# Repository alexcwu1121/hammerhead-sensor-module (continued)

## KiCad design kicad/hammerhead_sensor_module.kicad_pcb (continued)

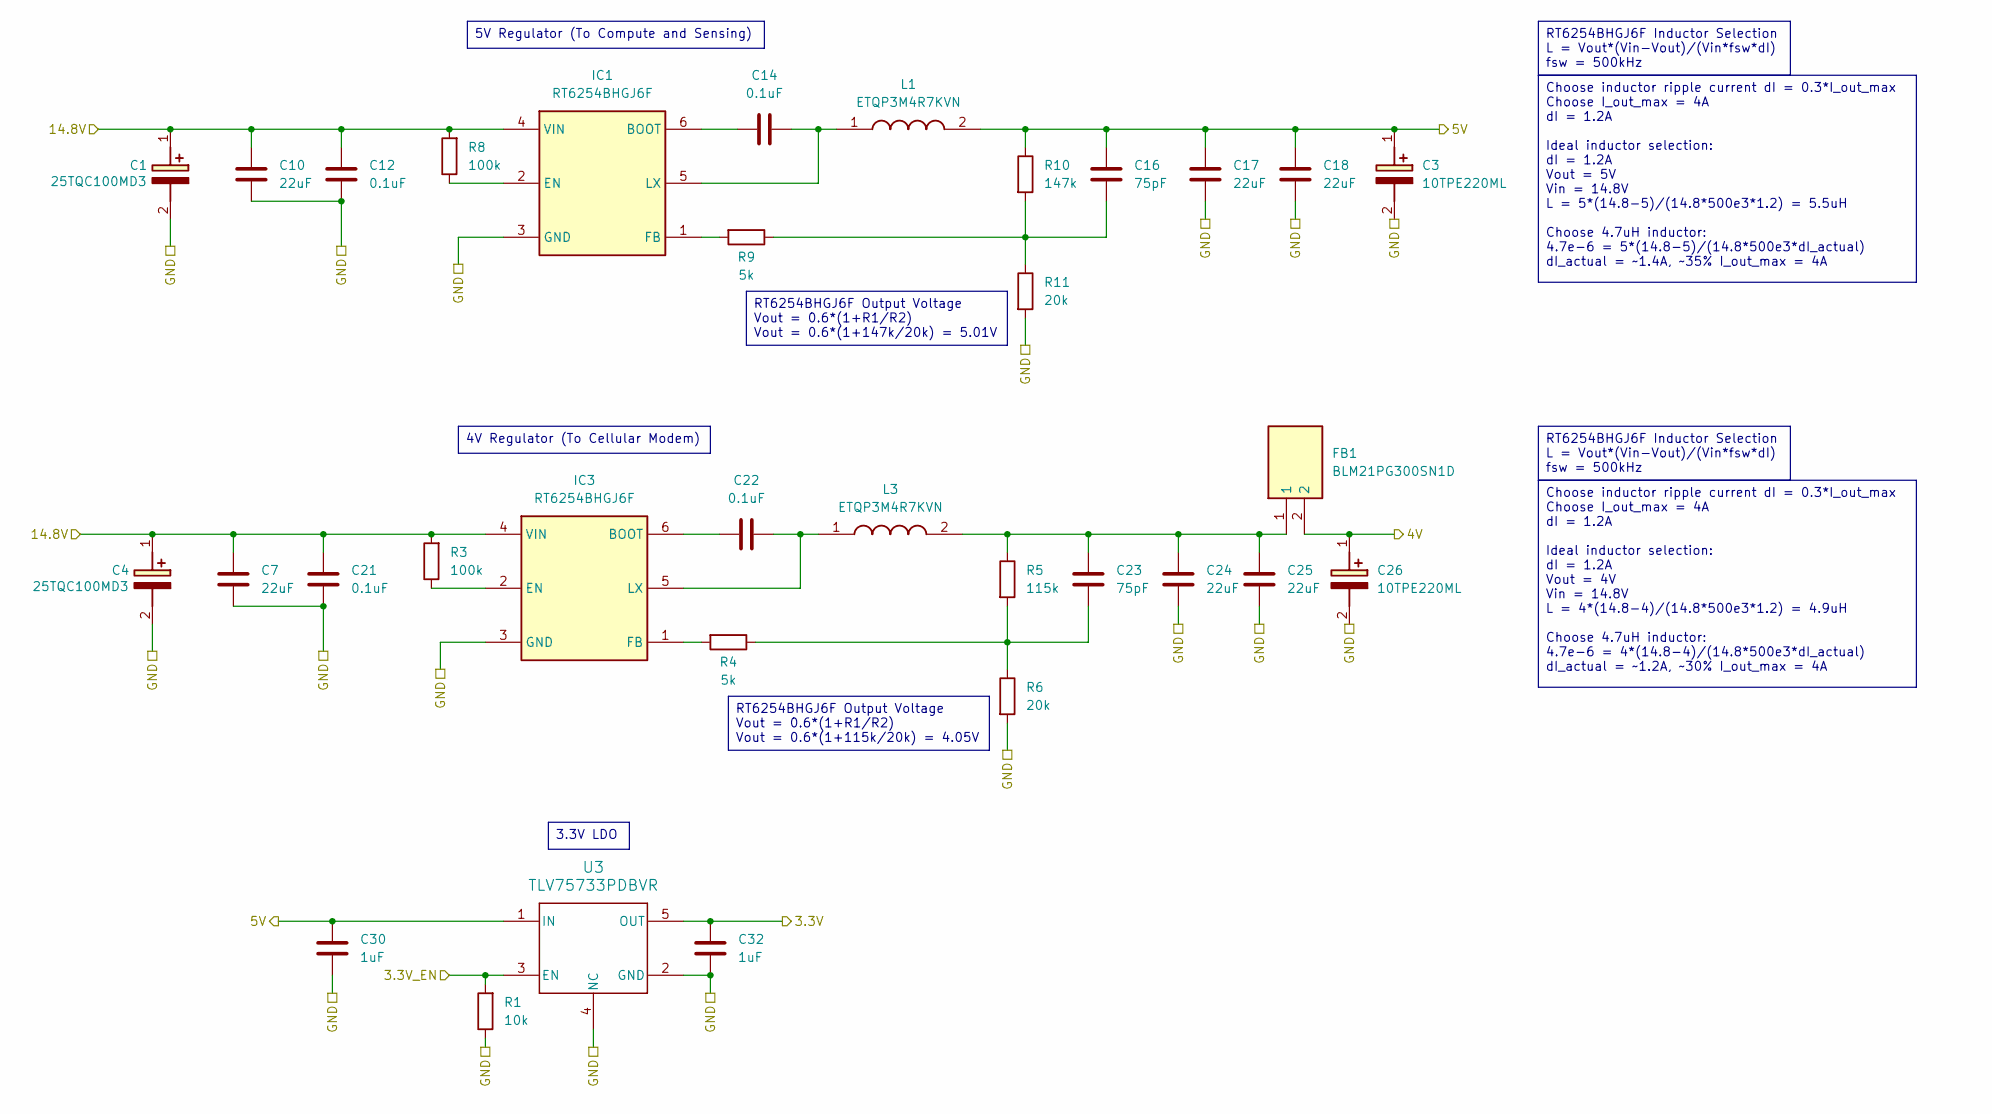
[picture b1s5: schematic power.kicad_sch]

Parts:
C1, C4: 25TQC100MD3; 16TDC150MYF; Manufacturer_Part_Number 25TQC100MD3; Mouser Part Number 667-25TQC100MD3
C3, C26: 10TPE220ML; 16TDC150MYF; Manufacturer_Part_Number 10TPE220ML; Mouser Part Number 667-10TPE220ML
C7, C10, C17, C18, C24, C25: 22uF; C_1206_3216Metric
C12, C14, C21, C22: 0.1uF; C_0201_0603Metric
C16, C23: 75pF; C_0201_0603Metric
C30, C32: 1uF; C_0201_0603Metric
FB1: BLM21PG300SN1D; BEADC2012X105N; Manufacturer_Part_Number BLM21PG300SN1D; Mouser Part Number 81-BLM21P300S
IC1, IC3: RT6254BHGJ6F; SOT95P280X100-6N; Manufacturer_Part_Number RT6254BHGJ6F; Mouser Part Number 835-RT6254BHGJ6F
L1, L3: ETQP3M4R7KVN; ETQP3M1R0KVN; Manufacturer_Part_Number ETQP3M4R7KVN
R1: 10k; R_0201_0603Metric
R3, R8: 100k; R_0201_0603Metric
R4, R9: 5k; R_0201_0603Metric
R5: 115k; R_0402_1005Metric
R6, R11: 20k; R_0201_0603Metric
R10: 147k; R_0402_1005Metric
U3: TLV75733PDBVR; DBV0005A_N

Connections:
3.3V: C32.1, U3.5 (OUT); also elsewhere on the board
4V: C26.1 (+), FB1.2; also elsewhere on the board
5V: C3.1 (+), C16.1, C17.1, C18.1, C30.1, L1.2, R10.1, U3.1 (IN); also elsewhere on the board
14.8V: C1.1 (+), C4.1 (+), C7.1, C10.1, C12.1, C21.1, IC1.4 (VIN), IC3.4 (VIN), R3.2, R8.2; also elsewhere on the board
/GPIO_VREF: R1.2, U3.3 (EN); also elsewhere on the board
GND: C1.2 (-), C3.2 (-), C4.2 (-), C7.2, C10.2, C12.2, C17.2, C18.2, C21.2, C24.2, C25.2, C26.2 (-), C30.2, C32.2, IC1.3 (GND), IC3.3 (GND), R1.1, R6.2, R11.2, U3.2 (GND), U3.4 (NC); also elsewhere on the board
unnamed: C16.2, R9.1, R10.2, R11.1
unnamed: C23.1, C24.1, C25.1, FB1.1, L3.2, R5.1
unnamed: C23.2, R4.1, R5.2, R6.1
unnamed: C14.1, IC1.6 (BOOT)
unnamed: IC1.2 (EN), R8.1
unnamed: IC1.1 (FB), R9.2
unnamed: C14.2, IC1.5 (LX), L1.1
unnamed: C22.1, IC3.6 (BOOT)
unnamed: IC3.2 (EN), R3.1
unnamed: IC3.1 (FB), R4.2
unnamed: C22.2, IC3.5 (LX), L3.1

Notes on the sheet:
Choose inductor ripple current dI = 0.3*I_out_max Choose I_out_max = 4A dI = 1.2A Ideal inductor selection: dI = 1.2A Vout = 5V Vin = 14.8V L = 5*(14.8-5)/(14.8*500e3*1.2) = 5.5uH Choose 4.7uH inductor: 4.7e-6 = 5*(14.8-5)/(14.8*500e3*dI_actual) dI_actual = ~1.4A, ~35% I_out_max = 4A
RT6254BHGJ6F Inductor Selection L = Vout*(Vin-Vout)/(Vin*fsw*dI) fsw = 500kHz
5V Regulator (To Compute and Sensing)
4V Regulator (To Cellular Modem)
RT6254BHGJ6F Output Voltage Vout = 0.6*(1+R1/R2) Vout = 0.6*(1+147k/20k) = 5.01V
3.3V LDO
RT6254BHGJ6F Output Voltage Vout = 0.6*(1+R1/R2) Vout = 0.6*(1+115k/20k) = 4.05V
Choose inductor ripple current dI = 0.3*I_out_max Choose I_out_max = 4A dI = 1.2A Ideal inductor selection: dI = 1.2A Vout = 4V Vin = 14.8V L = 4*(14.8-4)/(14.8*500e3*1.2) = 4.9uH Choose 4.7uH inductor: 4.7e-6 = 4*(14.8-4)/(14.8*500e3*dI_actual) dI_actual = ~1.2A, ~30% I_out_max = 4A

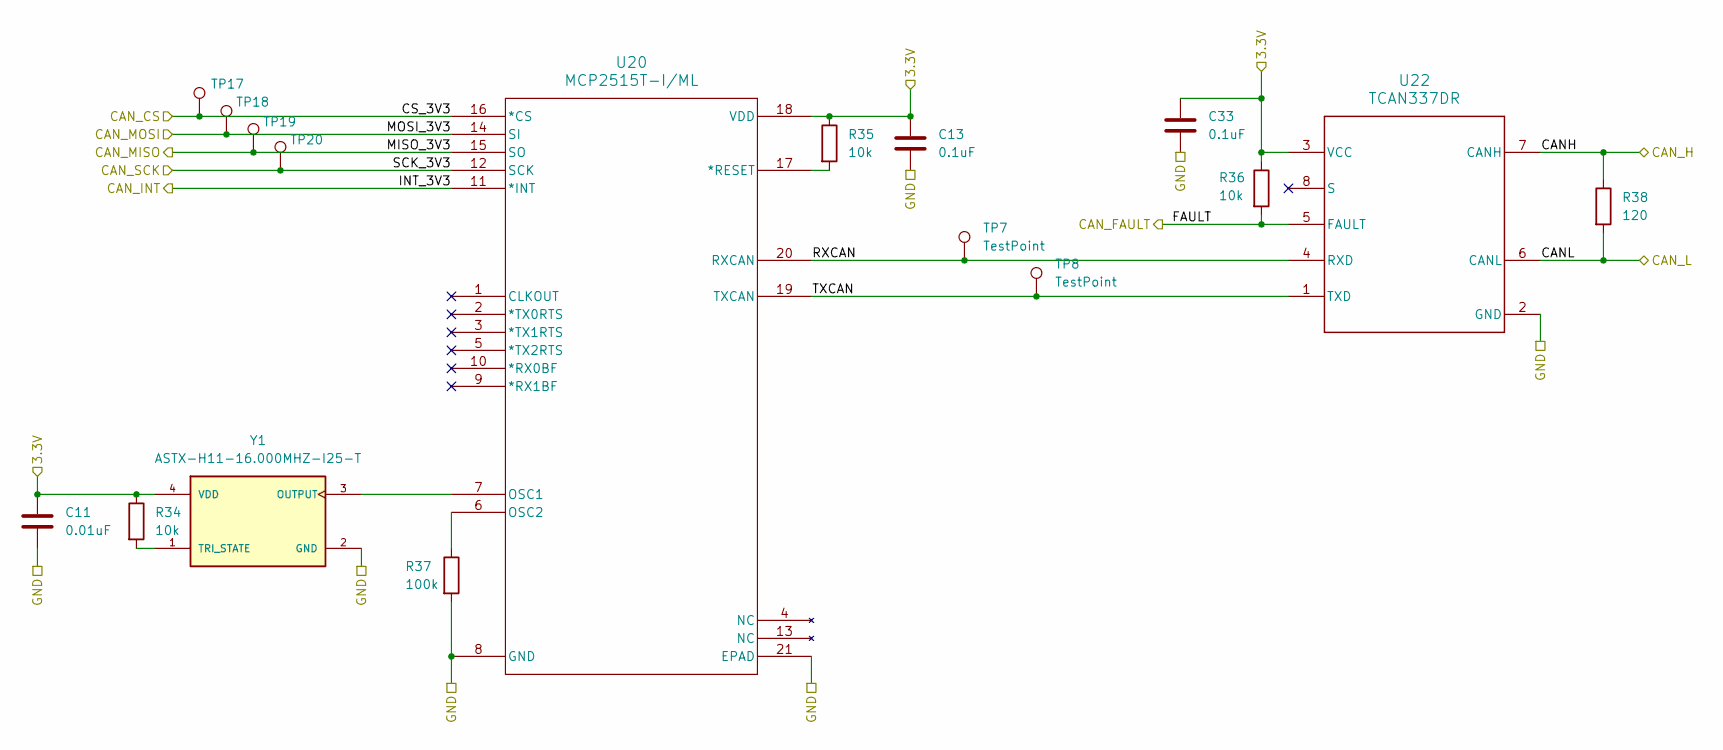
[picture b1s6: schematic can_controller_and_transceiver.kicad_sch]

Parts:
C11: 0.01uF; C_0402_1005Metric
C13, C33: 0.1uF; C_0402_1005Metric
R34, R35, R36: 10k; R_0402_1005Metric
R37: 100k; R_0402_1005Metric
R38: 120; R_0603_1608Metric
TP7, TP8, TP17, TP18, TP19, TP20: TestPoint; TestPoint_Pad_1.0x1.0mm
U20: MCP2515T-I/ML; QFN20_4x4MC_MCH
U22: TCAN337DR; D0008A_N
Y1: ASTX-H11-16.000MHZ-I25-T; XTAL_ASTX-H11-16.000MHZ-I25-T; PARTREV 05.13.15

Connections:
3.3V: C11.1, C13.1, C33.1, R34.1, R35.1, R36.1, U20.18 (VDD), U22.3 (VCC), Y1.4 (VDD); also elsewhere on the board
/CM5_GPIO/CAN Controller and Transceiver/RXCAN: TP7.1, U20.20 (RXCAN), U22.4 (RXD)
/CM5_GPIO/CAN Controller and Transceiver/TXCAN: TP8.1, U20.19 (TXCAN), U22.1 (TXD)
/CM5_GPIO/CAN_CS: TP17.1, U20.16 (*CS); also elsewhere on the board
/CM5_GPIO/CAN_FAULT: R36.2, U22.5 (FAULT); also elsewhere on the board
/CM5_GPIO/CAN_INT: U20.11 (*INT); also elsewhere on the board
/CM5_GPIO/CAN_MISO: TP19.1, U20.15 (SO); also elsewhere on the board
/CM5_GPIO/CAN_MOSI: TP18.1, U20.14 (SI); also elsewhere on the board
/CM5_GPIO/CAN_SCK: TP20.1, U20.12 (SCK); also elsewhere on the board
/PLATFORM_CANH: R38.1, U22.7 (CANH); also elsewhere on the board
/PLATFORM_CANL: R38.2, U22.6 (CANL); also elsewhere on the board
GND: C11.2, C13.2, C33.2, R37.2, U20.8 (GND), U20.21 (EPAD), U22.2 (GND), Y1.2 (GND); also elsewhere on the board
unnamed: R35.2, U20.17 (*RESET)
unnamed: U20.7 (OSC1), Y1.3 (OUTPUT)
unnamed: R37.1, U20.6 (OSC2)
unnamed: R34.2, Y1.1 (TRI_STATE)

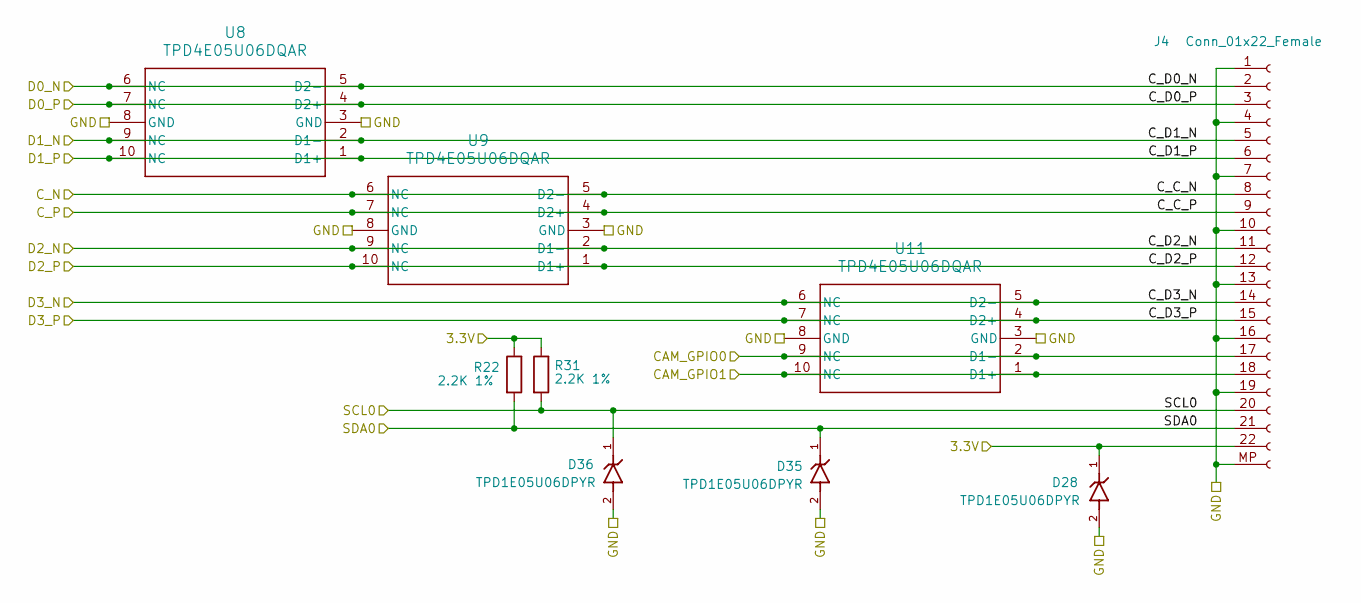
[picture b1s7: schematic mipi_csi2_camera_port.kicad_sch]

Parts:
D28, D35, D36: TPD1E05U06DPYR; SON65P60X100X45-2N
J4: Conn_01x22_Female; Hirose_FH12-22S-0.5SH_1x22-1MP_P0.50mm_Horizontal; Part Description 22 Position FFC, FPC Connector Contacts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
R22, R31: 2.2K 1%; R_0201_0603Metric; Part Description Resistor 2.2K M1005 1% 63mW
U8, U9, U11: TPD4E05U06DQAR; DQA0010A

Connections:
3.3V: D28.1, J4.22, R22.1, R31.1; also elsewhere on the board
/CAM_GPIO0: J4.17, U11.2 (D1-), U11.9 (NC); also elsewhere on the board
/CAM_GPIO1: J4.18, U11.1 (D1+), U11.10 (NC); also elsewhere on the board
/CM5_HighSpeed/DPHY0_C_N: J4.8, U9.5 (D2-), U9.6 (NC); also elsewhere on the board
/CM5_HighSpeed/DPHY0_C_P: J4.9, U9.4 (D2+), U9.7 (NC); also elsewhere on the board
/CM5_HighSpeed/DPHY0_D0_N: J4.2, U8.5 (D2-), U8.6 (NC); also elsewhere on the board
/CM5_HighSpeed/DPHY0_D0_P: J4.3, U8.4 (D2+), U8.7 (NC); also elsewhere on the board
/CM5_HighSpeed/DPHY0_D1_N: J4.5, U8.2 (D1-), U8.9 (NC); also elsewhere on the board
/CM5_HighSpeed/DPHY0_D1_P: J4.6, U8.1 (D1+), U8.10 (NC); also elsewhere on the board
/CM5_HighSpeed/DPHY0_D2_N: J4.11, U9.2 (D1-), U9.9 (NC); also elsewhere on the board
/CM5_HighSpeed/DPHY0_D2_P: J4.12, U9.1 (D1+), U9.10 (NC); also elsewhere on the board
/CM5_HighSpeed/DPHY0_D3_N: J4.14, U11.5 (D2-), U11.6 (NC); also elsewhere on the board
/CM5_HighSpeed/DPHY0_D3_P: J4.15, U11.4 (D2+), U11.7 (NC); also elsewhere on the board
/SCLO: D36.1, J4.20, R31.2; also elsewhere on the board
/SDAO: D35.1, J4.21, R22.2; also elsewhere on the board
GND: D28.2, D35.2, D36.2, J4.1, J4.4, J4.7, J4.10, J4.13, J4.16, J4.19, J4.MP, U8.3 (GND), U8.8 (GND), U9.3 (GND), U9.8 (GND), U11.3 (GND), U11.8 (GND); also elsewhere on the board

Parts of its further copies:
D17, D18, D29: TPD1E05U06DPYR; SON65P60X100X45-2N
J5: Conn_01x22_Female; Hirose_FH12-22S-0.5SH_1x22-1MP_P0.50mm_Horizontal; Part Description 22 Position FFC, FPC Connector Contacts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
R23, R24: 2.2K 1%; R_0201_0603Metric; Part Description Resistor 2.2K M1005 1% 63mW
U7, U10, U14: TPD4E05U06DQAR; DQA0010A

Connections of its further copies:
3.3V: D29.1, J5.22, R23.1, R24.1; also elsewhere on the board
/CAM_GPIO0: J5.17, U14.2 (D1-), U14.9 (NC); also elsewhere on the board
/CAM_GPIO1: J5.18, U14.1 (D1+), U14.10 (NC); also elsewhere on the board
/CM5_HighSpeed/DPHY1_C_N: J5.8, U10.5 (D2-), U10.6 (NC); also elsewhere on the board
/CM5_HighSpeed/DPHY1_C_P: J5.9, U10.4 (D2+), U10.7 (NC); also elsewhere on the board
/CM5_HighSpeed/DPHY1_D0_N: J5.2, U7.5 (D2-), U7.6 (NC); also elsewhere on the board
/CM5_HighSpeed/DPHY1_D0_P: J5.3, U7.4 (D2+), U7.7 (NC); also elsewhere on the board
/CM5_HighSpeed/DPHY1_D1_N: J5.5, U7.2 (D1-), U7.9 (NC); also elsewhere on the board
/CM5_HighSpeed/DPHY1_D1_P: J5.6, U7.1 (D1+), U7.10 (NC); also elsewhere on the board
/CM5_HighSpeed/DPHY1_D2_N: J5.11, U10.2 (D1-), U10.9 (NC); also elsewhere on the board
/CM5_HighSpeed/DPHY1_D2_P: J5.12, U10.1 (D1+), U10.10 (NC); also elsewhere on the board
/CM5_HighSpeed/DPHY1_D3_N: J5.14, U14.5 (D2-), U14.6 (NC); also elsewhere on the board
/CM5_HighSpeed/DPHY1_D3_P: J5.15, U14.4 (D2+), U14.7 (NC); also elsewhere on the board
/I2C_SCL_CAM2: D17.1, J5.20, R24.2; also elsewhere on the board
/I2C_SDA_CAM2: D18.1, J5.21, R23.2; also elsewhere on the board
GND: D17.2, D18.2, D29.2, J5.1, J5.4, J5.7, J5.10, J5.13, J5.16, J5.19, J5.MP, U7.3 (GND), U7.8 (GND), U10.3 (GND), U10.8 (GND), U14.3 (GND), U14.8 (GND); also elsewhere on the board

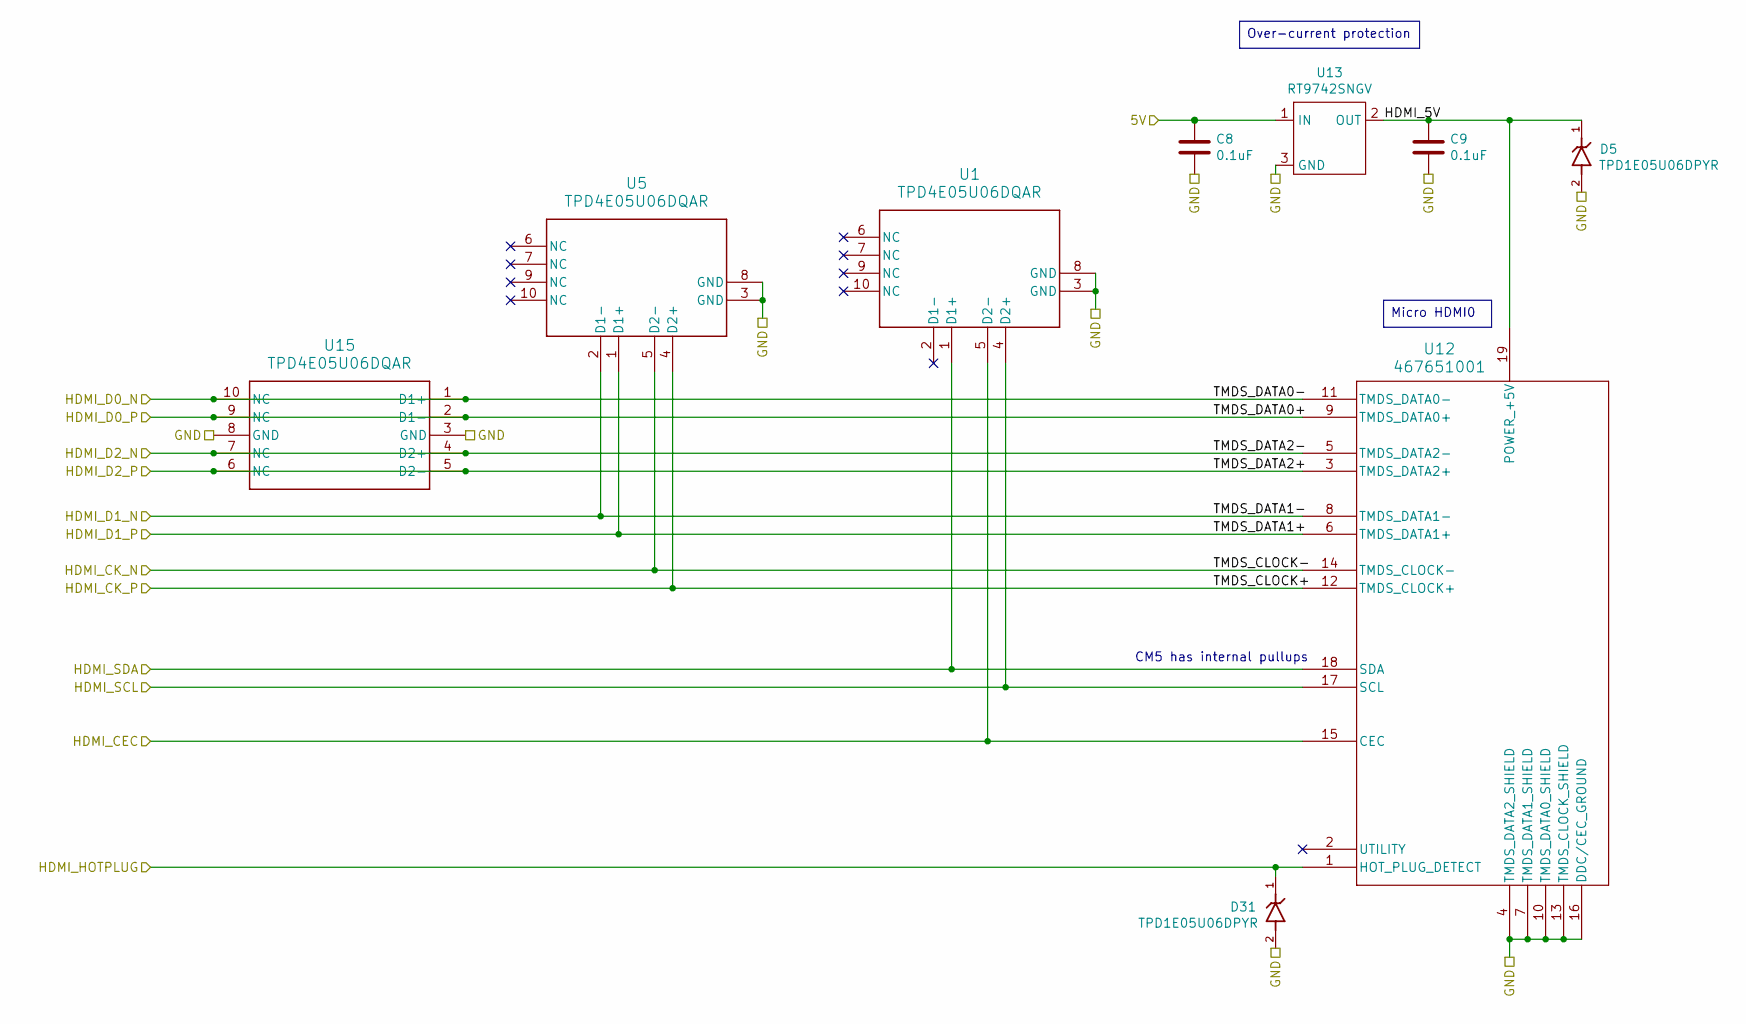
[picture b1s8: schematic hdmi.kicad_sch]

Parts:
C8, C9: 0.1uF; C_0402_1005Metric; Part Description 0.1uF 10% 16V Ceramic Capacitor X7R 040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
D5, D31: TPD1E05U06DPYR; SON65P60X100X45-2N
U1, U5, U15: TPD4E05U06DQAR; DQA0010A
U12: 467651001; 46765-1001_MOL
U13: RT9742SNGV; TSOT-23; Part Description Power Switch/Driver 1:1 N-Channel 500mA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

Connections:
5V: C8.1, U13.1 (IN); also elsewhere on the board
/CM5_HighSpeed/HDMI1_CEC: U1.5 (D2-), U12.15 (CEC); also elsewhere on the board
/CM5_HighSpeed/HDMI1_CK_N: U5.5 (D2-), U12.14 (TMDS_CLOCK-); also elsewhere on the board
/CM5_HighSpeed/HDMI1_CK_P: U5.4 (D2+), U12.12 (TMDS_CLOCK+); also elsewhere on the board
/CM5_HighSpeed/HDMI1_D0_N: U12.11 (TMDS_DATA0-), U15.1 (D1+), U15.10 (NC); also elsewhere on the board
/CM5_HighSpeed/HDMI1_D0_P: U12.9 (TMDS_DATA0+), U15.2 (D1-), U15.9 (NC); also elsewhere on the board
/CM5_HighSpeed/HDMI1_D1_N: U5.2 (D1-), U12.8 (TMDS_DATA1-); also elsewhere on the board
/CM5_HighSpeed/HDMI1_D1_P: U5.1 (D1+), U12.6 (TMDS_DATA1+); also elsewhere on the board
/CM5_HighSpeed/HDMI1_D2_N: U12.5 (TMDS_DATA2-), U15.4 (D2+), U15.7 (NC); also elsewhere on the board
/CM5_HighSpeed/HDMI1_D2_P: U12.3 (TMDS_DATA2+), U15.5 (D2-), U15.6 (NC); also elsewhere on the board
/CM5_HighSpeed/HDMI1_HOTPLUG: D31.1, U12.1 (HOT_PLUG_DETECT); also elsewhere on the board
/CM5_HighSpeed/HDMI1_SCL: U1.4 (D2+), U12.17 (SCL); also elsewhere on the board
/CM5_HighSpeed/HDMI1_SDA: U1.1 (D1+), U12.18 (SDA); also elsewhere on the board
/CM5_HighSpeed/hdmi/HDMI_5V: C9.1, D5.1, U12.19 (POWER_+5V), U13.2 (OUT)
GND: C8.2, C9.2, D5.2, D31.2, U1.3 (GND), U1.8 (GND), U5.3 (GND), U5.8 (GND), U12.4 (TMDS_DATA2_SHIELD), U12.7 (TMDS_DATA1_SHIELD), U12.10 (TMDS_DATA0_SHIELD), U12.13 (TMDS_CLOCK_SHIELD), U12.16 (DDC/CEC_GROUND), U13.3 (GND), U15.3 (GND), U15.8 (GND); also elsewhere on the board

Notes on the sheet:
CM5 has internal pullups
Micro HDMI0
Over-current protection

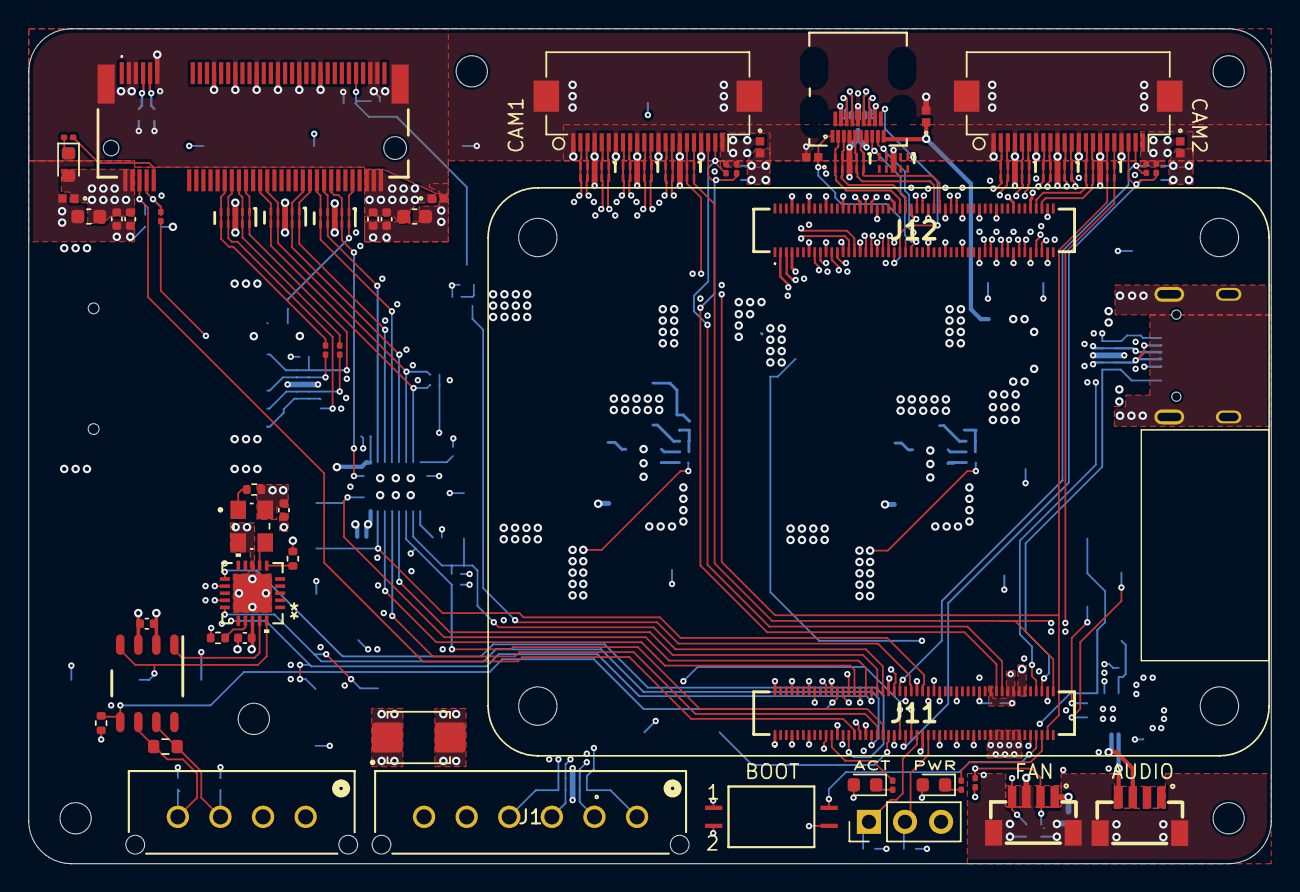
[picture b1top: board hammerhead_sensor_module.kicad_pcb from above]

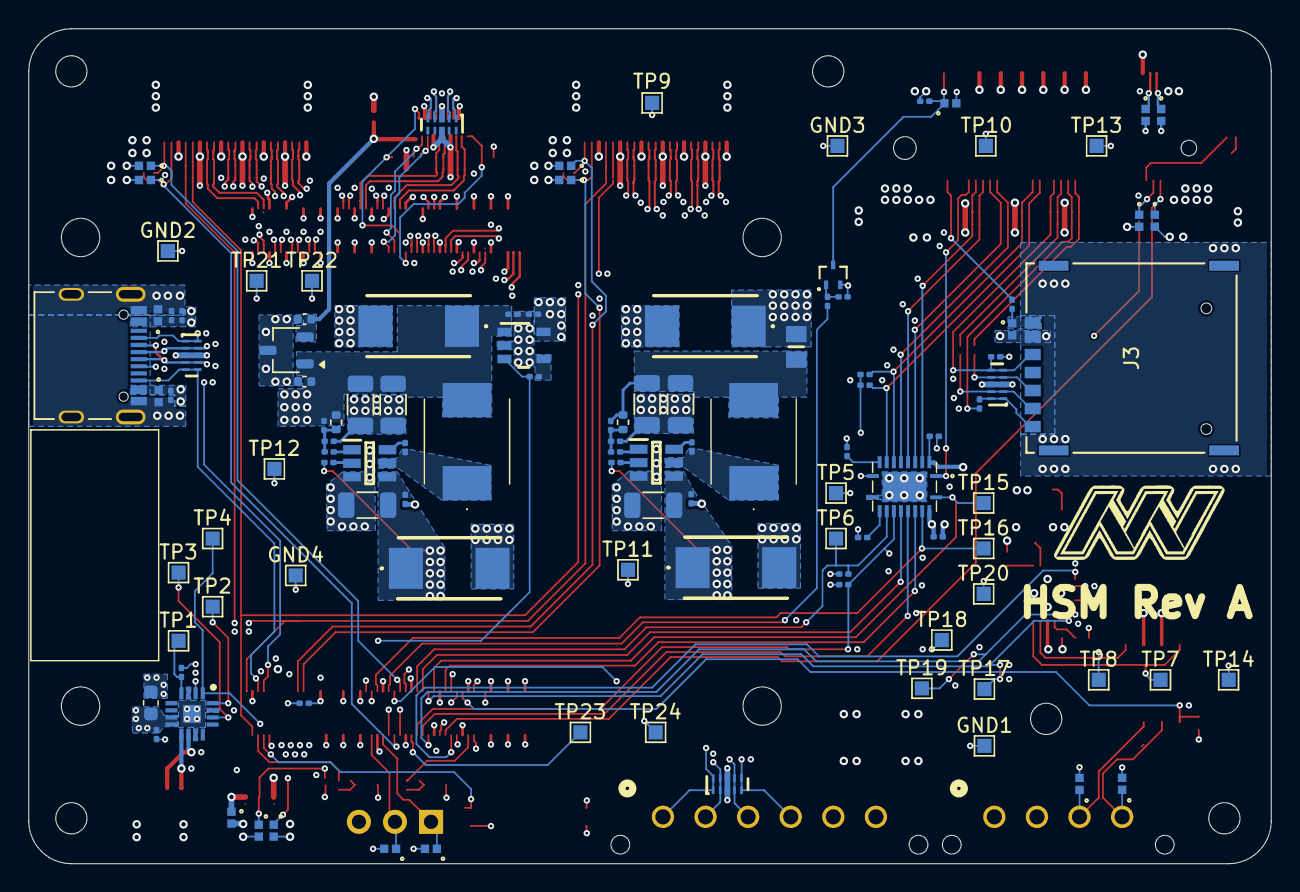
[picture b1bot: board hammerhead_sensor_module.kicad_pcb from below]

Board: 6 copper layers, 87.5 x 58.8 mm, 175 parts (113 on the bottom side), 131 nets.

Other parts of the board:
Module1: ComputeModule5-CM5; Raspberry-Pi-5-Compute-Module

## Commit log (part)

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2026-03-21 upload kicad design files
